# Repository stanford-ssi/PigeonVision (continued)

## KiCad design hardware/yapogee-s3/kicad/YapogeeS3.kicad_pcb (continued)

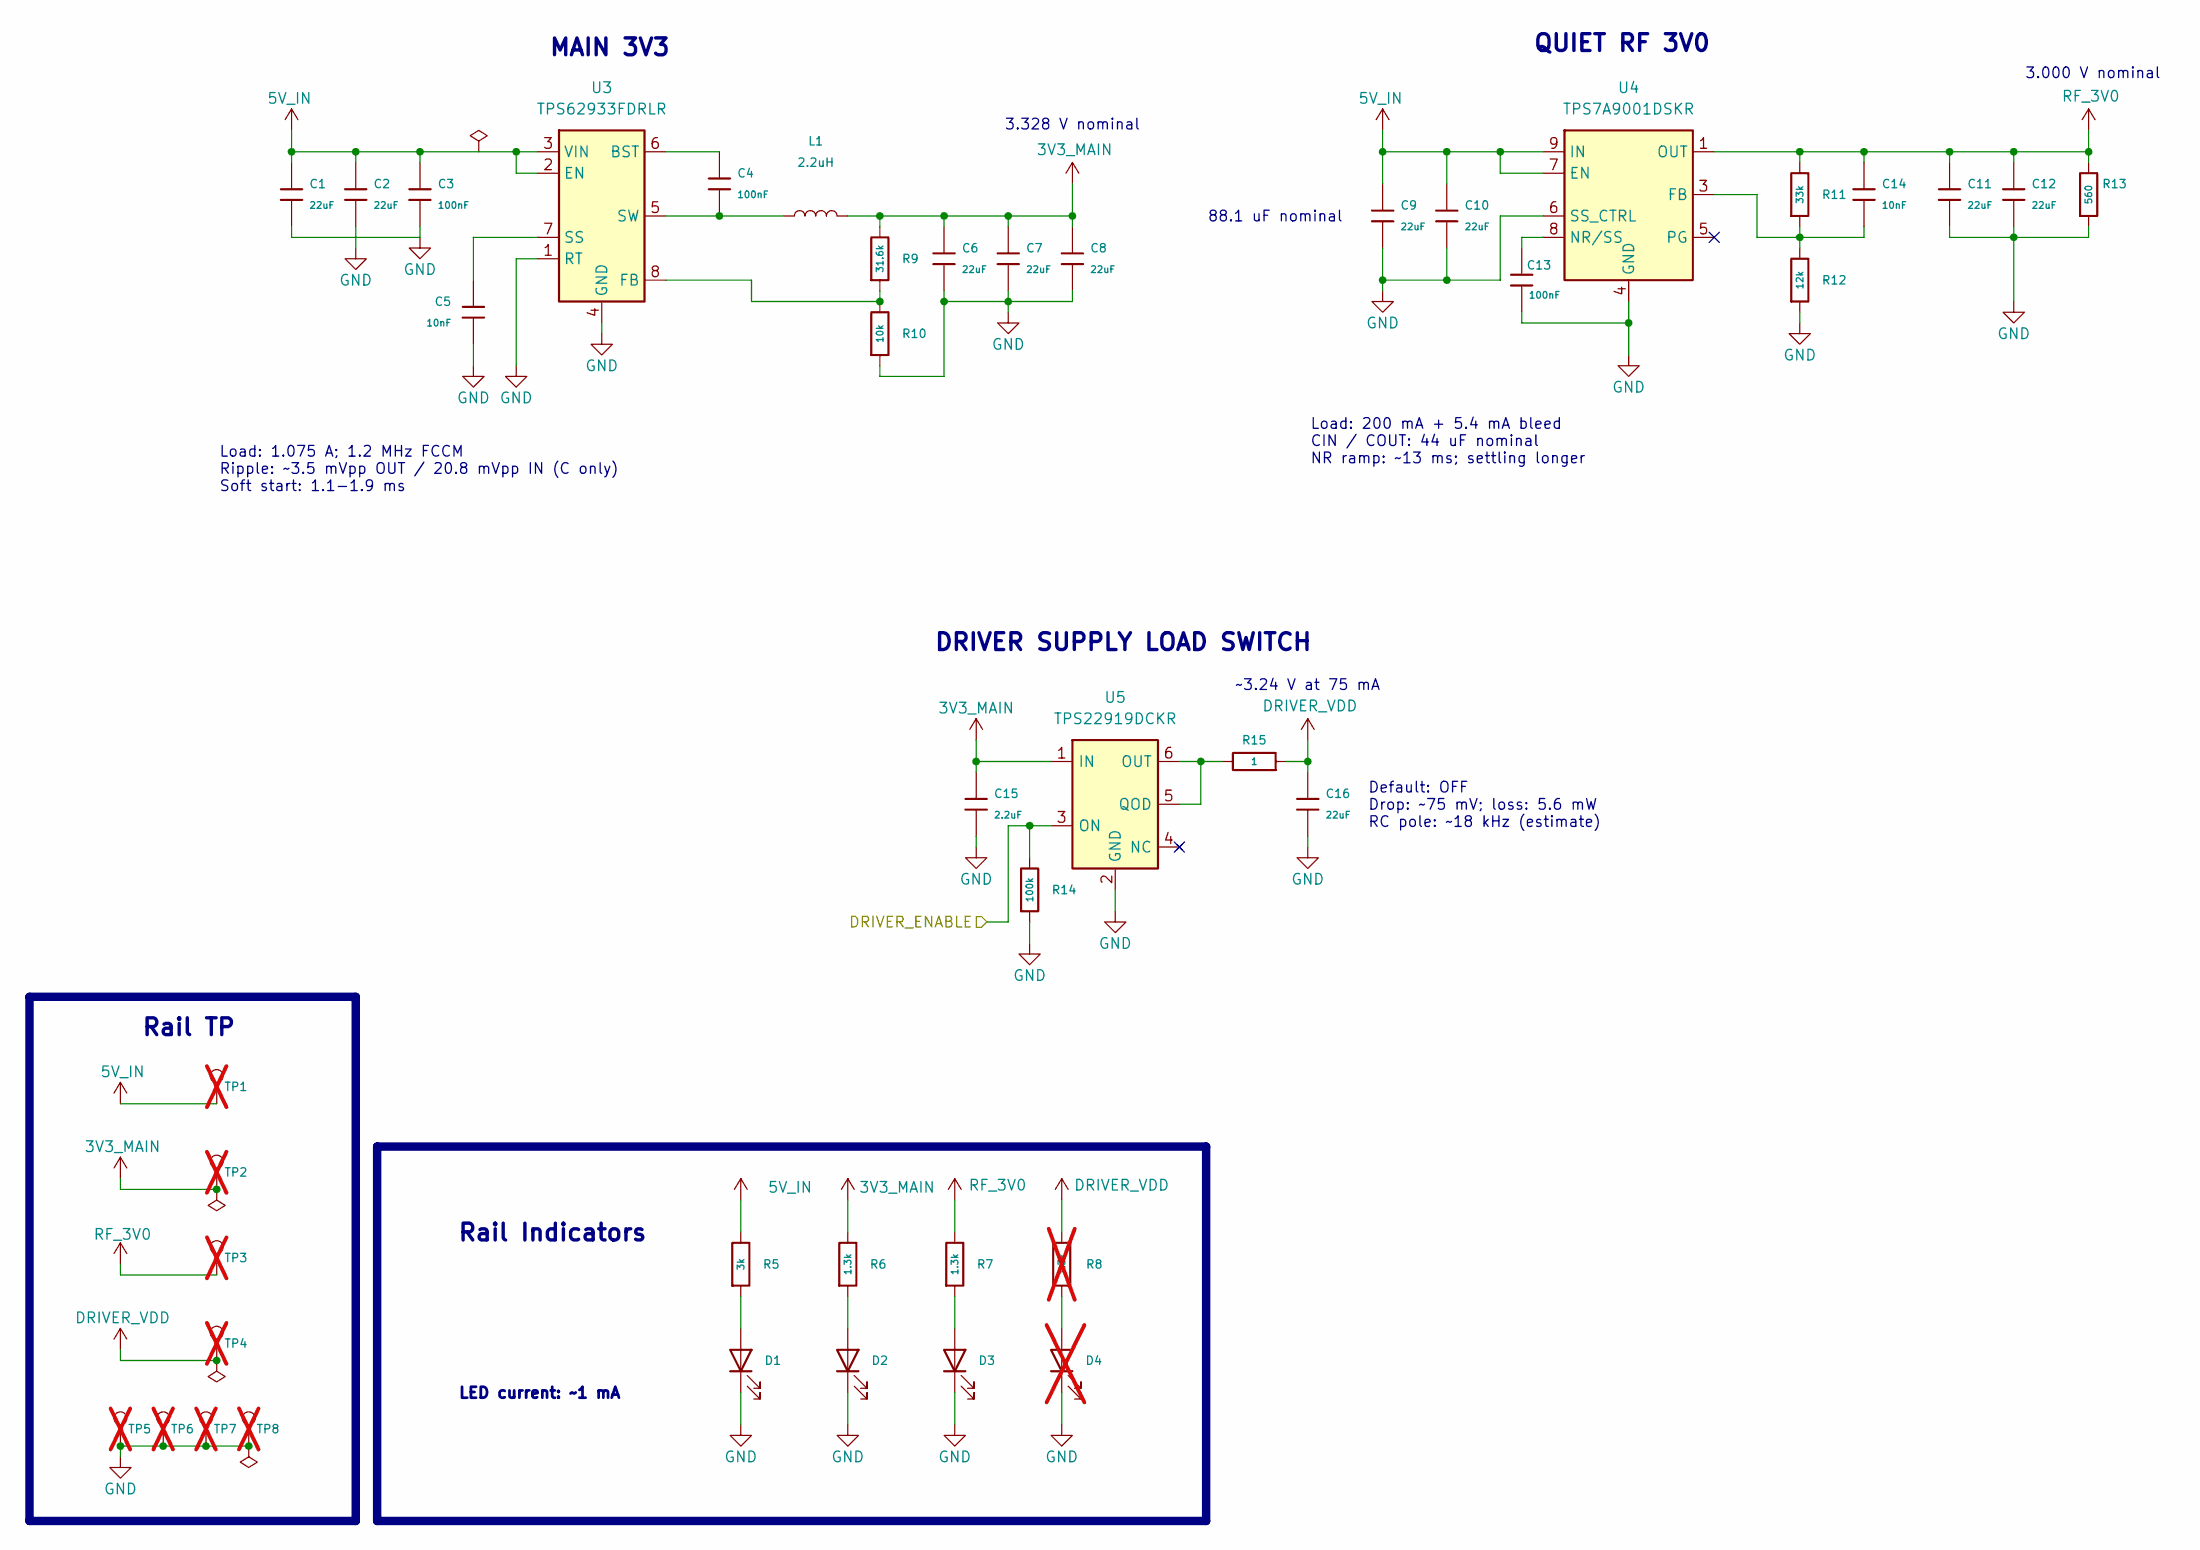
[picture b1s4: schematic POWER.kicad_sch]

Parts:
C1, C2, C6, C7, C8, C9, C10, C11, C12, C16: 22uF; C_Murata_GCM31_3216_RefReflow; Voltage Rated 10V; Tolerance ±10%; MPN GCM31CR71A226KE02L; LCSC C126598
C3, C4, C13: 100nF; C_Murata_GCM15_1005_RefReflow; Voltage Rated 50V; Tolerance ±10%; MPN GCM155R71H104KE02D; LCSC C85858
C5, C14: 10nF; C_Murata_GCM18_1608_RefReflow; Voltage Rated 50V; Tolerance ±5%; MPN GCM1885C1H103JA16D; LCSC C1517789
C15: 2.2uF; C_Kyocera_KAM15_1608_RefReflow; Voltage Rated 10V; Tolerance ±10%; MPN KAM15AR71A225KT; DigiKey Part # 478-KAM15AR71A225KTCT-ND
D1, D2, D3: LTST-C170KGKT; LiteOn_LTST-C170KGKT_0805; MPN LTST-C170KGKT; DigiKey Part # 160-1414-1-ND
D4: LTST-C170KGKT; LiteOn_LTST-C170KGKT_0805; MPN LTST-C170KGKT; DigiKey Part # 160-1414-1-ND; not fitted
L1: 2.2uH; Bourns_SRP5030TA; MPN SRP5030TA-2R2M
R5: 3k; KiCad_Resistor_SMD_R_0402_1005Metric; Tolerance ±1%; Part CRCW04023K00FKED
R6, R7: 1.3k; KiCad_Resistor_SMD_R_0402_1005Metric; Tolerance ±1%; Part CRCW04021K30FKED
R8: 1.3k; KiCad_Resistor_SMD_R_0402_1005Metric; Tolerance ±1%; Part CRCW04021K30FKED; not fitted
R9: 31.6k; KiCad_Resistor_SMD_R_0402_1005Metric; MPN RT0402BRD0731K6L
R10: 10k; KiCad_Resistor_SMD_R_0402_1005Metric; MPN RT0402BRD0710KL
R11: 33k; KiCad_Resistor_SMD_R_0402_1005Metric; MPN RT0402BRD0733KL
R12: 12k; KiCad_Resistor_SMD_R_0402_1005Metric; MPN RT0402BRD0712KL
R13: 560; KiCad_Resistor_SMD_R_0402_1005Metric; MPN RC0402FR-07560RL
R14: 100k; KiCad_Resistor_SMD_R_0402_1005Metric; MPN RC0402FR-07100KL
R15: 1; KiCad_Resistor_SMD_R_0402_1005Metric; MPN CRCW04021R00FKED
TP1: 5V_IN; TestPoint_Pad_D1.0mm; MPN PCB_TEST_PAD_1MM; not fitted
TP2: 3V3_MAIN; TestPoint_Pad_D1.0mm; MPN PCB_TEST_PAD_1MM; not fitted
TP3: RF_3V0; TestPoint_Pad_D1.0mm; MPN PCB_TEST_PAD_1MM; not fitted
TP4: DRIVER_VDD; TestPoint_Pad_D1.0mm; MPN PCB_TEST_PAD_1MM; not fitted
TP5, TP6, TP7, TP8: GND; TestPoint_Pad_D1.0mm; MPN PCB_TEST_PAD_1MM; not fitted
U3: TPS62933FDRLR; SOT-583-8; MPN TPS62933FDRLR; LCSC Part # C5219272
U4: TPS7A9001DSKR; TI_DSK0010A_TPS7A90; MPN TPS7A9001DSKR
U5: TPS22919DCKR; TI_DCK0006A_SC70-6_P0.65mm; MPN TPS22919DCKR; LCSC Part # C2149796

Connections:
3V3_MAIN: C6.1, C7.1, C8.1, C15.1, L1.2, R6.1, R9.1, TP2.1, U5.1 (IN); also elsewhere on the board
5V_IN: C1.1, C2.1, C3.1, C9.1, C10.1, R5.1, TP1.1, U3.2 (EN), U3.3 (VIN), U4.7 (EN), U4.9 (IN), U4.10 (IN); also elsewhere on the board
/MCU/DRIVER_ENABLE: R14.1, U5.3 (ON); also elsewhere on the board
DRIVER_VDD: C16.1, R8.1, R15.2, TP4.1; also elsewhere on the board
GND: C1.2, C2.2, C3.2, C5.2, C6.2, C7.2, C8.2, C9.2, C10.2, C11.2, C12.2, C13.2, C15.2, C16.2, D1.1 (K), D2.1 (K), D3.1 (K), D4.1 (K), R10.2, R12.2, R13.2, R14.2, TP5.1, TP6.1, TP7.1, TP8.1, U3.1 (RT), U3.4 (GND), U4.4 (GND), U4.6 (SS_CTRL), U4.11 (GND), U5.2 (GND); also elsewhere on the board
unnamed: D1.2 (A), R5.2
unnamed: D2.2 (A), R6.2
unnamed: D3.2 (A), R7.2
unnamed: D4.2 (A), R8.2
unnamed: C4.1, U3.6 (BST)
unnamed: R9.2, R10.1, U3.8 (FB)
unnamed: C5.1, U3.7 (SS)
unnamed: C4.2, L1.1, U3.5 (SW)
unnamed: C14.2, R11.2, R12.1, U4.3 (FB)
unnamed: C13.1, U4.8 (NR/SS)
unnamed: R15.1, U5.5 (QOD), U5.6 (OUT)
RF_3V0: C11.1, C12.1, C14.1, R7.1, R11.1, R13.1, TP3.1, U4.1 (OUT), U4.2 (OUT); also elsewhere on the board

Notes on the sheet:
Rail Indicators
88.1 uF nominal
Load: 1.075 A; 1.2 MHz FCCM Ripple: ~3.5 mVpp OUT / 20.8 mVpp IN (C only) Soft start: 1.1-1.9 ms
Rail TP
MAIN 3V3
DRIVER SUPPLY LOAD SWITCH
Load: 200 mA + 5.4 mA bleed CIN / COUT: 44 uF nominal NR ramp: ~13 ms; settling longer
QUIET RF 3V0
3.328 V nominal
~3.24 V at 75 mA
LED current: ~1 mA
3.000 V nominal
Default: OFF Drop: ~75 mV; loss: 5.6 mW RC pole: ~18 kHz (estimate)

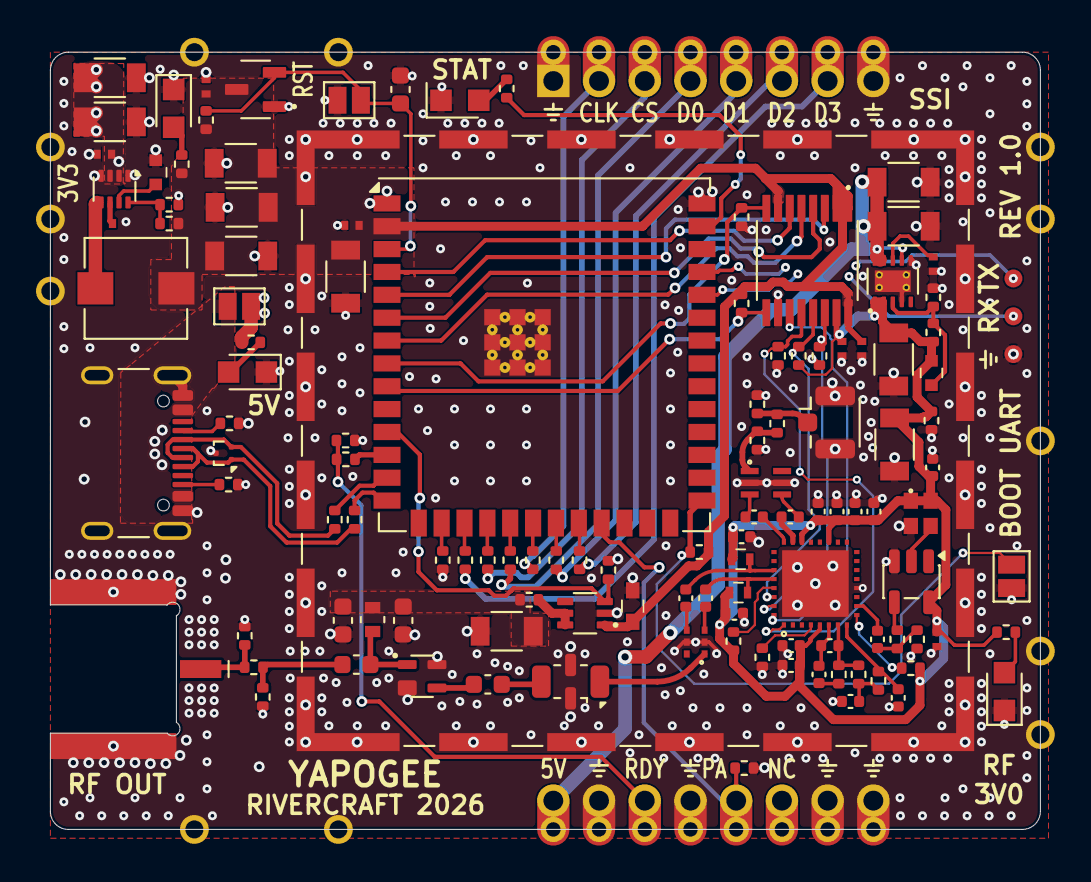
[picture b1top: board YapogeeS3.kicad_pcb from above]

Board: 4 copper layers, 55.0 x 43.2 mm, 124 parts (0 on the bottom side), 83 nets.

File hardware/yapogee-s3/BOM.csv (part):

block,references,quantity,value,manufacturer,mpn,package,population,symbol,footprint,datasheet
MCU,U1,1,"ESP32-S3 module,16MB QSPI flash,8MB octal PSRAM",Espressif,ESP32-S3-WROOM-1U-N16R8,18x19.2mm 40 perimeter pads + GND EP41,Fitted,PigeonVision:ESP32-S3-WROOM-1U-N16R8,PigeonVision:Espressif_ESP32_S3_WROOM_1U_18x19.2mm,https://www.espressif.com/sites/default/files/documentation/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
MCU,C17,1,100nF,Murata,GCM155R71H104KE02D,0402,Fitted,Yapogee_Power:GCM155R71H104KE02D,PigeonVision:C_Murata_GCM15_1005_RefReflow,https://pim.murata.com/asset/pim4/ceramicCapacitorSMD/GCM155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
MCU,C18,1,22uF,Murata,GCM31CR71A226KE02L,1206,Fitted,Yapogee_Power:GCM31CR71A226KE02L,PigeonVision:C_Murata_GCM31_3216_RefReflow,https://www.murata.com/en-us/products/productdetail?partno=G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
MCU,"R16,R17",2,10k,Yageo,RC0402FR-0710KL,0402,Fitted,PigeonVision:RC0402FR-0710KL,PigeonVision:KiCad_Resistor_SMD_R_0402_1005Metric,https://www.yageo.com/en/Chart/Download/pdf/RC0402
MCU,R18,1,10k,Yageo,RC0402FR-0710KL,0402,Fitted,PigeonVision:RC0402FR-0710KL,PigeonVision:KiCad_Resistor_SMD_R_0402_1005Metric,https://www.yageo.com/en/Chart/Download/pdf/RC0402
MCU,C19,1,1uF X7R 16V 10%,TDK,C1608X7R1C105K080AC,0603,Fitted,PigeonVision:C1608X7R1C105K080AC,PigeonVision:KiCad_Capacitor_SMD_C_0603_1608Metric,https://product.tdk.com/en/search/capacitor/ceramic/mlcc/inf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
MCU,U6,1,3.08V reset supervisor 200ms,Texas Instruments,TLV803EA30DBZR,SOT23-3 DBZ,Fitted,PigeonVision:TLV803EA30DBZR,PigeonVision:TI_DBZ0003A_TLV803E,https://www.ti.com/lit/ds/symlink/tlv803e.pdf
MCU,C21,1,100nF,Murata,GCM155R71H104KE02D,0402,Fitted,Yapogee_Power:GCM155R71H104KE02D,PigeonVision:C_Murata_GCM15_1005_RefReflow,https://pim.murata.com/asset/pim4/ceramicCapacitorSMD/GCM155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
USB,J2,1,USB-C2.0 power/data receptacle,GCT,USB4105-GF-A-060,16contact topmount;0.60mm shell stakes,Fitted,PigeonVision:USB4105-GF-A-060,PigeonVision:USB_C_Receptacle_GCT_USB4105_GF_A_16P,https://gct.co/files/drawings/usb4105.pdf
USB,U2,1,2-channel passive USB D+/D− ESD,Texas Instruments,TPD2EUSB30DRTR,"SOT-3 DRT,1.0x0.8mm body",Fitted,Yapogee:TPD2EUSB30DRTR,PigeonVision:TI_DRT0003A_TPD2EUSB30,https://www.ti.com/lit/ds/symlink/tpd2eusb30.pdf
USB,"R3,R4",2,22,Yageo,RC0402FR-0722RL,0402,Fitted,PigeonVision:RC0402FR-0722RL,PigeonVision:KiCad_Resistor_SMD_R_0402_1005Metric,https://www.yageo.com/en/Chart/Download/pdf/RC0402
INTERFACE,U9,1,RF mixer control level isolation,Texas Instruments,SN74AXC4T774PWR,TSSOP16 PW,Fitted,PigeonVision:SN74AXC4T774PWR,PigeonVision:TI_PW0016A_SN74AXC4T774,https://www.ti.com/lit/ds/symlink/sn74axc4t774.pdf
INTERFACE,"C28,C29",2,100nF,Murata,GCM155R71H104KE02D,0402,Fitted,Yapogee_Power:GCM155R71H104KE02D,PigeonVision:C_Murata_GCM15_1005_RefReflow,https://pim.murata.com/asset/pim4/ceramicCapacitorSMD/GCM155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
INTERFACE,R21,1,4.7k,Yageo,RC0402FR-074K7L,0402,Fitted,PigeonVision:RC0402FR-074K7L,PigeonVision:KiCad_Resistor_SMD_R_0402_1005Metric,https://www.yageo.com/en/Chart/Download/pdf/RC0402
INTERFACE,R22,1,10k,Yageo,RC0402FR-0710KL,0402,Fitted,PigeonVision:RC0402FR-0710KL,PigeonVision:KiCad_Resistor_SMD_R_0402_1005Metric,https://www.yageo.com/en/Chart/Download/pdf/RC0402
INTERFACE,R23,1,100k,Yageo,RC0402FR-07100KL,0402,Fitted,PigeonVision:RC0402FR-07100KL,PigeonVision:KiCad_Resistor_SMD_R_0402_1005Metric,https://www.yageo.com/en/Chart/Download/pdf/RC0402
INTERFACE,"R26,R27,R28,R29,R30,R31,R32",7,33,Yageo,RC0402FR-0733RL,0402,Fitted,PigeonVision:RC0402FR-0733RL,PigeonVision:KiCad_Resistor_SMD_R_0402_1005Metric,https://www.yageo.com/en/Chart/Download/pdf/RC0402
INTERFACE,R33,1,4.7k,Yageo,RC0402FR-074K7L,0402,Fitted,PigeonVision:RC0402FR-074K7L,PigeonVision:KiCad_Resistor_SMD_R_0402_1005Metric,https://www.yageo.com/en/Chart/Download/pdf/RC0402
INTERFACE,"R34,R35",2,10k,Yageo,RC0402FR-0710KL,0402,Fitted,PigeonVision:RC0402FR-0710KL,PigeonVision:KiCad_Resistor_SMD_R_0402_1005Metric,https://www.yageo.com/en/Chart/Download/pdf/RC0402
Interface,R36,1,100k,Yageo,RC0402FR-07100KL,0402,Fitted,PigeonVision:RC0402FR-07100KL,PigeonVision:KiCad_Resistor_SMD_R_0402_1005Metric,https://www.yageo.com/en/
USB,"R1,R2",2,5.1k,Yageo,RC0402FR-075K1L,0402,Fitted,Yapogee:RC0402FR-075K1L,PigeonVision:KiCad_Resistor_SMD_R_0402_1005Metric,https://www.lcsc.com/datasheet/lcsc_datasheet_2206010045_UNI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
MCU,D5,1,green rail/status LED,Lite-On,LTST-C170KGKT,0805,Fitted,Yapogee_Power:LTST-C170KGKT,PigeonVision:LiteOn_LTST-C170KGKT_0805,https://optoelectronics.liteon.com/upload/download/DS22-2000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
MCU,R19,1,1k,Yageo,RC0402FR-071KL,0402,Fitted,PigeonVision:RC0402FR-071KL,PigeonVision:KiCad_Resistor_SMD_R_0402_1005Metric,https://www.yageo.com/en/Chart/Download/pdf/RC0402
POWER,"C1,C2,C6,C7,C8,C9,C11,C16",8,22uF,Murata,GCM31CR71A226KE02L,1206,Fitted,Yapogee_Power:GCM31CR71A226KE02L,PigeonVision:C_Murata_GCM31_3216_RefReflow,https://www.murata.com/en-us/products/productdetail?partno=G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
POWER,"C3,C4,C13",3,100nF,Murata,GCM155R71H104KE02D,0402,Fitted,Yapogee_Power:GCM155R71H104KE02D,PigeonVision:C_Murata_GCM15_1005_RefReflow,https://pim.murata.com/asset/pim4/ceramicCapacitorSMD/GCM155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
POWER,"C5,C14",2,10nF,Murata,GCM1885C1H103JA16D,0603,Fitted,Yapogee_Power:GCM1885C1H103JA16D,PigeonVision:C_Murata_GCM18_1608_RefReflow,https://pim.murata.com/asset/pim4/ceramicCapacitorSMD/GCM188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
POWER,"C10,C12",2,22uF,Murata,GCM31CR71A226KE02L,1206,Fitted,Yapogee_Power:GCM31CR71A226KE02L,PigeonVision:C_Murata_GCM31_3216_RefReflow,https://www.murata.com/en-us/products/productdetail?partno=G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
POWER,C15,1,2.2uF,KYOCERA AVX,KAM15AR71A225KT,0603,Fitted,Yapogee_Power:KAM15AR71A225KT,PigeonVision:C_Kyocera_KAM15_1608_RefReflow,https://spec.ele.kyocera.com/specifications/KAM15AR71A225KT.pdf
POWER,"D1,D2,D3,D4",4,LTST-C170KGKT,Lite-On,LTST-C170KGKT,0805,Fitted,Yapogee_Power:LTST-C170KGKT,PigeonVision:LiteOn_LTST-C170KGKT_0805,https://optoelectronics.liteon.com/upload/download/DS22-2000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
POWER,L1,1,2.2uH,Bourns,SRP5030TA-2R2M,5.7±0.3 x5.2±0.2 x2.8±0.2mm SMD,Fitted,Yapogee_Power:SRP5030TA-2R2M,PigeonVision:Bourns_SRP5030TA,https://www.bourns.com/docs/product-datasheets/srp5030ta.pdf
POWER,R5,1,3k,Vishay,CRCW04023K00FKED,0402,Fitted,Yapogee_Power:CRCW04023K00FKED,PigeonVision:KiCad_Resistor_SMD_R_0402_1005Metric,https://www.vishay.com/doc?20035=
POWER,"R6,R7,R8",3,1.3k,Vishay,CRCW04021K30FKED,0402,Fitted,Yapogee_Power:CRCW04021K30FKED,PigeonVision:KiCad_Resistor_SMD_R_0402_1005Metric,https://www.vishay.com/doc?20035=
POWER,R9,1,31.6k,Yageo,RT0402BRD0731K6L,0402,Fitted,PigeonVision:RT0402BRD0731K6L,PigeonVision:KiCad_Resistor_SMD_R_0402_1005Metric,https://www.yageo.com/en/Chart/Download/pdf/RT0402
POWER,R10,1,10k,Yageo,RT0402BRD0710KL,0402,Fitted,PigeonVision:RT0402BRD0710KL,PigeonVision:KiCad_Resistor_SMD_R_0402_1005Metric,https://www.yageo.com/en/Chart/Download/pdf/RT0402
POWER,R11,1,33k,Yageo,RT0402BRD0733KL,0402,Fitted,PigeonVision:RT0402BRD0733KL,PigeonVision:KiCad_Resistor_SMD_R_0402_1005Metric,https://www.yageo.com/en/Chart/Download/pdf/RT0402
POWER,R12,1,12k,Yageo,RT0402BRD0712KL,0402,Fitted,PigeonVision:RT0402BRD0712KL,PigeonVision:KiCad_Resistor_SMD_R_0402_1005Metric,https://www.yageo.com/en/Chart/Download/pdf/RT0402
POWER,R13,1,560,Yageo,RC0402FR-07560RL,0402,Fitted,PigeonVision:RC0402FR-07560RL,PigeonVision:KiCad_Resistor_SMD_R_0402_1005Metric,https://www.yageo.com/en/Chart/Download/pdf/RC0402
POWER,R14,1,100k,Yageo,RC0402FR-07100KL,0402,Fitted,PigeonVision:RC0402FR-07100KL,PigeonVision:KiCad_Resistor_SMD_R_0402_1005Metric,https://www.yageo.com/en/Chart/Download/pdf/RC0402
POWER,R15,1,1,Vishay Dale,CRCW04021R00FKED,0402,Fitted,PigeonVision:CRCW04021R00FKED,PigeonVision:KiCad_Resistor_SMD_R_0402_1005Metric,https://www.vishay.com/docs/20035/dcrcwe3.pdf
POWER,U3,1,TPS62933FDRLR,Texas Instruments,TPS62933FDRLR,SOT583-8 DRL,Fitted,PigeonVision:TPS62933FDRLR,PigeonVision:SOT-583-8,https://www.ti.com/lit/ds/symlink/tps62933.pdf
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
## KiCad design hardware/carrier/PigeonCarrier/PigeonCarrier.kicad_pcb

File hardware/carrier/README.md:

# Carrier

[Rev 1.1 fabrication and assembly files](production/Rev1.1/README.md)

**Current plan:** one CM5, two cameras, SPI to [Yapogee S3](../yapogee-s3/README.md) and Ethernet for service or the E200 fallback. Yapogee uses an ESP32-S3-WROOM-1U-N16R8 module and converts its RF output to 1.28 GHz. The PA and filter are on a separate board. Record to eMMC. Use a 3S 5 Ah battery with a one-hour planning target including pad time. Carrier diameter is 5.7 in (144.78 mm).

[Edit diagram](block-diagram.drawio) · [KiCad project](PigeonCarrier/PigeonCarrier.kicad_pro) · [Design master](../../calculations/design-master.xlsx)

| Block | Parts / connection |
| --- | --- |
| Compute | SC1596 / CM5104064: 4 GB RAM, 64 GB eMMC |
| CM5 connectors | 2 × Amphenol 10164227-1001A1RLF, 1.5 mm stack |
| Cameras | 2 × FRAMOS IMX900 + CIL212; retain the working FRAMOS adapters. J7/J8 use vertical Hirose FH12-22S-0.5SVA(54) FFC connectors with CM5IO-style pinout |
| Input protection | LM74502DDFR, 2 × CSD18540Q5B, SMBJ18CA; unfused input |
| Main 5 V | LM61495RPHR; CM5 and Yapogee, with E200 as an alternate transmitter |
| RF 5 V | TPS62933FDRLR; separate supply, default off |
| Camera rail | TPS62933FDRLR: shared 3V3_CAM from VBAT, enabled by 3V3_CM5; adapter boards provide camera-specific rails |
| Battery monitor | INA226AIDGSR + WSL25125L000FEA18, 5 mΩ |
| Sensors | BMI088, BMP581 and INA226 on CM5 GPIO2/3 I²C; polling without interrupt wiring |
| Camera control | Dedicated CM5 camera I²C lines; CAM0_RST from J1.97 and CAM1_RST from J1.100. Synchronization access reserved, synchronized exposures not required |
| Ethernet | EDAC A70-112-331N126 with integrated magnetics |
| Service | USB-C data/recovery, nRPIBOOT shunt, PWR_BUT button, J12 debug UART and CM5 activity LED on carrier; separate USB-C, BOOT, reset and UART access on Yapogee |
| Flight UART | Receive required; return TX optional. Logic voltage, connector and protocol TBD |

Both camera connectors receive the shared 3V3_CAM rail; MIPI connects directly to CM5. Keep the working adapter boards and their camera-specific power sequencing. The carrier does not replace their internal regulator circuitry.

Sensors use CM5 3.3 V. Yapogee receives 5V_MAIN through castellations and makes its own 3.328 V main and quiet 3.0 V rails. Reserve 1.5 A for the daughterboard. Its USB-C port supports standalone power before installation from a known 5 V source providing at least 1.5 A. Once mounted, leave JP1 open and use USB for data only while the carrier is on. Independent Pi PMIC-off operation is unsupported. The selected GRF5613 PA uses the separate switched 5V_RF rail. Keep space, 5 V power and Ethernet for the E200 fallback. The bench input is a PJ-102AH barrel jack beside the battery connector, used with the battery unplugged.

J1 uses vertical AMASS XT60PB-M30.G.Y: pin 1, at the keyed end marked −, is GND; pin 2, at the flat end marked +, is VBAT_RAW. J6 and both camera connectors are also vertical. USB-C J10 and the PJ-102AH bench input J2 remain horizontal. [Connector geometry, sourcing and model limits](../libraries/review/vertical-connectors.md).

J13 is the 55 × 43.18 mm Yapogee landing below the CM5. Its 28 lands match the module castellations, including twelve extra GND anchors. The footprint omits paste for hand soldering. The closed SMA pocket measures 33 × 12 mm with R1.5 corners and leaves about 11.3 mm of board at the narrowest point of the outer rim. It clears the body of the Amphenol 135103-01-06.00 elbow as it first meets the jack with the cable pointing up. Check the mating sequence, wrench access and cable bend in the flight stack before fabrication. [Cable assembly](https://www.amphenolrf.com/en-us/part/135103-01-06-00/5975/) The E200 stays available as a separate placement option. [Module interface](../yapogee-s3/interfaces.md)

| Signal | CM5 GPIO | CM5 J3 pad | Yapogee J1 / carrier J13 pad |
| --- | ---: | ---: | ---: |
| SCLK | 11 | 38 | 2 |
| D0 / MOSI | 10 | 44 | 5 |
| D1 | 9 | 40 | 7 |
| CS_N | 8 | 39 | 4 |
| READY | 25 | 41 | 11 |
| PA request into Pi | 22 | 46 | 13 |
| 5V_MAIN | — | — | 3 |
| D2 and D3, reserved for quad | — | — | 8, 10 |
| Reserved | — | — | 14 |

R42 pulls CS_N up to 3V3_CM5 with 4.7 kΩ. The CM5 and Yapogee share ground and use direct 3.3 V I/O. Power the installed Yapogee from 5V_MAIN and keep JP1 open. Coordinate GPIO startup and shutdown to avoid driving an unpowered endpoint.

Single-lane SPI0 is the bring-up mode. D1 provides a path to dual transmit with driver and firmware changes. Native SPI0 quad needs GPIO0 and GPIO1, which are assigned to CAM1 I²C. A quad implementation needs a different pin or host-peripheral plan and bench validation. [CM5 GPIO mux](https://datasheets.raspberrypi.com/cm5/cm5-datasheet.pdf)

GPIO17 / J3.50 switches the RF buck through 5V_RF_EN and retains its 10 kΩ pull-down. GPIO22 / J3.46 receives the Yapogee request. GPIO23 / J3.47 drives the separate, active-high PA_BIAS_EN signal.

The top sheet shows the six CM5-to-Yapogee signals and the separate PA bias enable wire. J14 is the vertical Molex 0430450418 Micro-Fit 3.0 header. Pin 1 supplies 5V_RF (4.88 V nominal), pins 2 and 4 are ground, and pin 3 carries PA_BIAS_EN. The PA board pulls pin 3 low by default and handles the GRF5613 shutdown polarity locally. J14 sits beside the RF buck and uses the same Molex STEP model as the PA board. PA control firmware remains pending. [PA harness and power](../rf-frontend/README.md)

J12 is a JST SH BM03B-SRSS-TB debug UART on CM5 GPIO14/15 using the Raspberry Pi debug-connector pinout: 1 RX into the CM5 (GPIO15), 2 GND, 3 TX from the CM5 (GPIO14). A Raspberry Pi Debug Probe plugs in with a straight-through cable. Both lines have 1 kΩ series resistors. The specification calls for 100 Ω, but CM5 GPIO pads are not failsafe, so the larger value limits back-feed from a powered probe into an unpowered CM5. LED4 (via R41, 220 Ω from 3V3_CM5) shows CM5 activity on LED_nACT.

CM5 configuration implied by this carrier: set `PSU_MAX_CURRENT=5000` in the bootloader EEPROM, because CC1/CC2 are unconnected and no USB-PD negotiation occurs. Set `enable_uart=1` for a Linux console on J12. Set `force_eeprom_read=0`, because ID_SD/ID_SC carry the CAM1 I²C bus.

Power control: J6 on Regulators uses vertical AMASS XT30UPB-M.G.Y. Pin 1 connects directly to U1 pin 1 (EN/UVLO / PWR_EN); pin 2 is GND. This dry-contact switch intentionally uses the connector's −-marked end for PWR_EN and +-marked end for GND; the moulded signs do not describe supply polarity. Use the microswitch COM and NO terminals: with the pin inserted and the lever pressed, closed contacts ground EN/UVLO and turn power off. Removing the pin releases the lever and opens the contact, allowing the existing UVLO divider to enable power. Confirm that the actual mechanism gives these contact states. An unplugged switch also allows power. This is not a latch: shut down the CM5 before reinserting the pin.

Q4, R39 and R40 were removed from the schematic and unrouted PCB. At 12.6 V, the closed contact carries 12.6 V / 7.5 kΩ = 1.68 mA through R2; R2 dissipates 21.2 mW. The existing UVLO and OV dividers remain unchanged. Total off-state divider draw is about 1.89 mA, plus controller current and leakage. Off disables downstream battery power; it does not isolate the battery or eliminate standby current. Switch contact quality, bounce and startup remain bench checks. [LM74502 datasheet](https://www.ti.com/lit/ds/symlink/lm74502.pdf).

Camera, sensor, Ethernet and USB/service hierarchy is connected, along with CM5 power/grounds and both regulator enables. The carrier USB-C port uses host VBUS only for data-switch control, with no connection to the battery or 5 V power rail. Its ESD footprint uses explicit external copper connections from each protected pad to the opposite NC pad. USB enumeration, recovery and power transitions remain hardware checks. The cooler fan header uses the native CM5 PWM/tach interface with 5V_MAIN supply.

The 2026-10-06 direct-switch check reported no ERC errors or warnings. All 200 CM5 contacts were connected or intentionally marked unused. The switch change affected only J6.1 among the retained component connections. Power-source flags identify feeds through passive parts, including U7's internally charged bootstrap node. Switch contact states, camera adapter current and sequencing, XT60 fit, power transitions and final layout remain to be checked. [Switch verification](../../build/pull-pin-direct-2026-10-06/verification.json) · [Connection review](../../build/carrier-closeout-2026-10-05/connection-review.json) · [Footprint review](../../build/carrier-closeout-2026-10-05/all-footprints-audit.json)

## Routing

Use **JLC06161H-3313**, 1.6 mm nominal, 1 oz outer and 0.5 oz inner copper. Route signals on F.Cu, L3 (In2.Cu) and B.Cu. Reserve L2 (In1.Cu), L4 (In3.Cu) and L5 (In4.Cu) for continuous GND. Add and fill those zones during layout.

| Net class | Outer width / gap | L3 width / gap | P/N skew |
| --- | --- | --- | --- |
| CSI and Ethernet, 100 Ω | 0.150 / 0.500 mm | 0.125 / 0.300 mm | 0.15 mm max |
| USB 2.0, 90 Ω | 0.175 / 0.300 mm | 0.160 / 0.300 mm | 0.15 mm max |
| Single ended, 50 Ω | 0.160 mm | 0.140 mm | n/a |

Layer rules select the L3 geometry automatically. SPI SCLK, D0, D1 and CS_N use SE_50R; I²C, UART and slow controls keep their normal classes. Power widths remain starting values: 1.50 mm battery, 1.00 mm 5 V and 0.50 mm 3.3 V. Use short outer-layer pours for the high-current paths.

Route CAM1 west of the SMA pocket. Keep the CM5 launch short before opening to the ordinary pair gap. Copper-to-edge clearance remains 0.50 mm. Use 0.45 mm via lands with 0.30 mm drills for controlled-impedance nets and 0.60 / 0.30 mm for general routing. The smaller vias fit the camera connector lands but need a staggered escape from the 0.20 mm-wide CM5 lands. No blind, buried or laser microvias are enabled.

The outer model references L2 or L5; L3 references L2 and L4. Keep other same-layer copper 0.50 mm away outside the reviewed launches. Match P/N within each pair and keep each camera's long runs on the same layer where practical. Review clock-to-data skew before tuning; the CM5 datasheet provides no numeric CSI interlane limit. [Calculations](routing-plan.json) · [Fabrication notes](fabrication-notes.md) · [CM5 datasheet](https://datasheets.raspberrypi.com/cm5/cm5-datasheet.pdf)

The BMP581 uses the shared solder mask opening recommended by Bosch. Keep exposed copper under the sensor limited to its intended pads and escapes. [BMP581 datasheet](https://www.bosch-sensortec.com/media/boschsensortec/downloads/datasheets/bst-bmp581-ds004.pdf)

The design master still budgets E200 power. Reconcile it with the accepted 1.5 A Yapogee allocation on 5V_MAIN, keeping E200 as an alternative rather than adding both transmitter loads to one flight configuration. GRF5613 is selected for PA planning; its loaded current and thermal performance remain unmeasured. Confirm mounting and connector access before final layout.

[Library and sourcing](../libraries/README.md) · [CM5 datasheet](https://datasheets.raspberrypi.com/cm5/cm5-datasheet.pdf) · [Camera datasheet](https://www.mouser.com/catalog/specsheets/FRAMOS_2-12-2026_FSM.GO-IMX900_Datasheet_v1.2a.pdf)

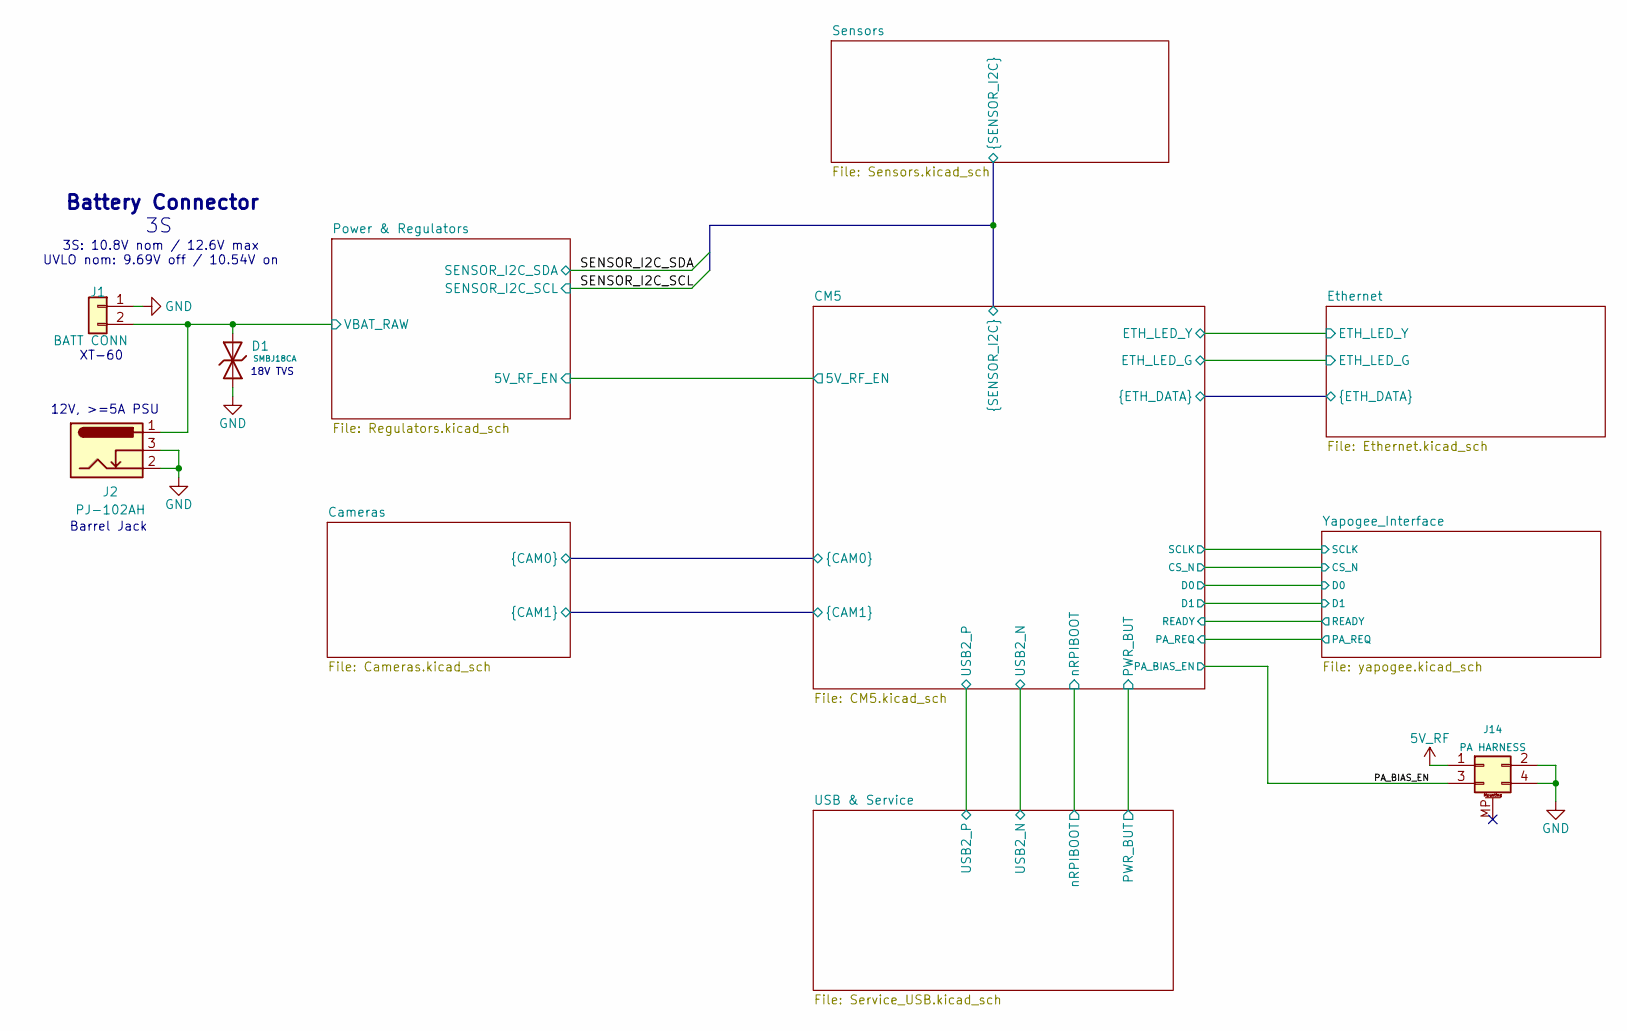
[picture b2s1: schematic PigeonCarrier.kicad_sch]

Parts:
D1: SMBJ18CA; D_SMB; Part SMBJ18CA; LCSC C19077574
J1: BATT CONN; AMASS_XT60PB-M_1x02_P7.20mm_Vertical_2025; MPN XT60PB-M30.G.Y; LCSC C19268037
J2: PJ-102AH; SameSky_PJ-102AH_Horizontal; Voltage / Current Rating 24 V / 5 A (manufacturer); MPN PJ-102AH; DigiKey Part # CP-102AH-ND
J14: PA HARNESS; Molex_Micro-Fit_3.0_43045-0418_2x02-1MP_P3.00mm_Vertical; MPN 0430450418

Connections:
5V_RF: J14.1 (5V_RF); also elsewhere on the board
/PA_BIAS_EN: J14.3 (PA_BIAS_EN); also elsewhere on the board
/Power & Regulators/VBAT_RAW: D1.2, J1.2, J2.1 (Center); also elsewhere on the board
GND: D1.1, J1.1, J2.2 (Sleeve), J2.3 (Sleeve_Shunt), J14.2 (GND), J14.4 (GND); also elsewhere on the board

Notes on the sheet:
Barrel Jack
Battery Connector
XT-60
3S: 10.8V nom / 12.6V max UVLO nom: 9.69V off / 10.54V on
18V TVS
12V, >=5A PSU

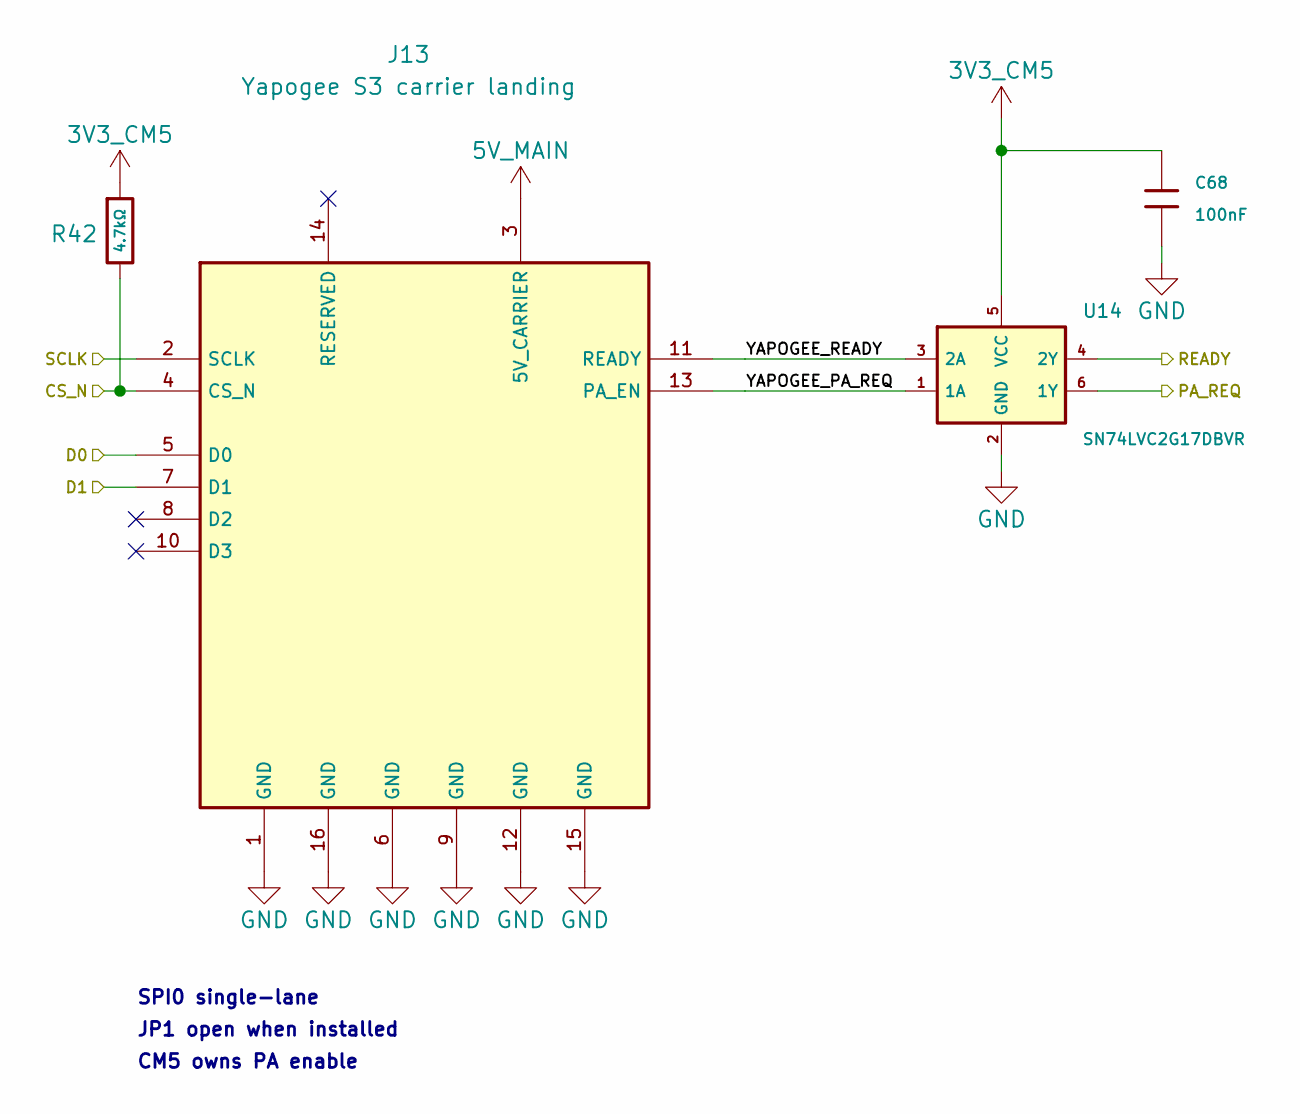
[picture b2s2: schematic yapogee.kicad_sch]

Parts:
C68: 100nF; C_0402; Voltage Rated 50V; Tolerance u00b110%; Part CL05B104KB54PNC; LCSC C307331
J13: Yapogee S3 carrier landing; YapogeeS3_CarrierLanding16_55x43p18_P2p54_GND12
R42: 4.7kΩ; R_0402; Overload Voltage (Max) 50V; Tolerance ±1%; Part 0402WGF4701TCE; LCSC C25900
U14: SN74LVC2G17DBVR; SOT-23-6; MPN SN74LVC2G17DBVR; LCSC C10429

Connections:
3V3_CM5: C68.1, R42.1, U14.5 (VCC); also elsewhere on the board
5V_MAIN: J13.3 (5V_CARRIER); also elsewhere on the board
/CM5/CS_N: J13.4 (CS_N), R42.2; also elsewhere on the board
/CM5/D0: J13.5 (D0); also elsewhere on the board
/CM5/D1: J13.7 (D1); also elsewhere on the board
/CM5/PA_REQ: U14.6 (1Y); also elsewhere on the board
/CM5/READY: U14.4 (2Y); also elsewhere on the board
/CM5/SCLK: J13.2 (SCLK); also elsewhere on the board
/Yapogee_Interface/YAPOGEE_PA_REQ: J13.13 (PA_EN), U14.1 (1A)
/Yapogee_Interface/YAPOGEE_READY: J13.11 (READY), U14.3 (2A)
GND: C68.2, J13.1 (GND), J13.6 (GND), J13.9 (GND), J13.12 (GND), J13.15 (GND), J13.16 (GND), U14.2 (GND); also elsewhere on the board

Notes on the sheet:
JP1 open when installed
SPI0 single-lane
CM5 owns PA enable

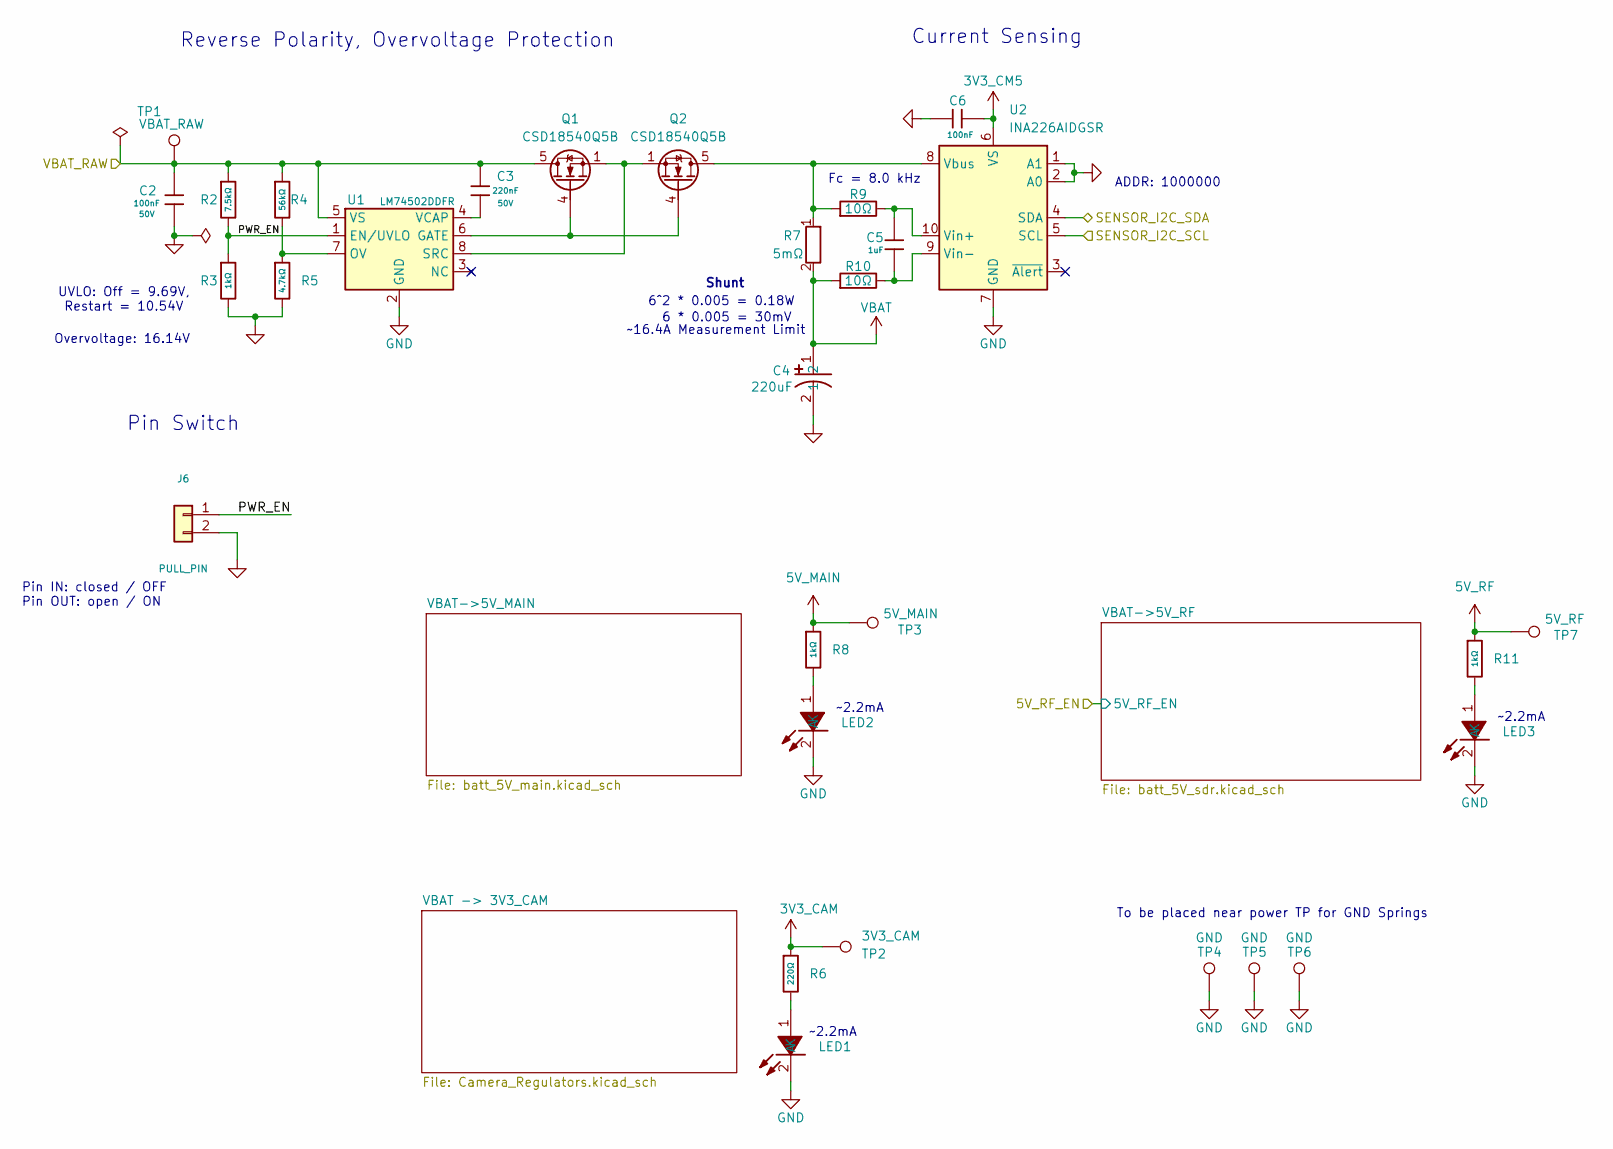
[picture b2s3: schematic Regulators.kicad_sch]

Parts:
C2, C6: 100nF; C_0402; Voltage Rated 50V; Tolerance ±10%; Part CL05B104KB54PNC; LCSC C307331
C3: 220nF; C_0805; Voltage Rated 50V; Tolerance ±10%; Part CL21B224KBFNNNE; LCSC C5378
C4: 220uF; Panasonic_EEE-FK1V221P_CaseF_8x10.2mm; Manufacturer Part EEEFK1V221P; LCSC C178562
C5: 1uF; C_0805; Voltage Rated 50V; Tolerance ±10%; Part CL21B105KBFNNNE; LCSC C28323
J6: PULL_PIN; AMASS_XT30UPB-M_1x02_P5.00mm_Vertical_2025; MPN XT30UPB-M.G.Y; LCSC Part # C428721
LED1, LED2, LED3: 0805G_Green; Manufacturer Part KT-0805G; LCSC C2297
Q1, Q2: CSD18540Q5B; TI_CSD18540Q5B_Q5B; MPN CSD18540Q5B; LCSC C86513
R2: 7.5kΩ; R_0402; Overload Voltage (Max) 50V; Tolerance ±1%; Part 0402WGF7501TCE; LCSC C25918
R3, R8, R11: 1kΩ; R_0402; Overload Voltage (Max) 50V; Tolerance ±1%; Part 0402WGF1001TCE; LCSC C11702
R4: 56kΩ; R_0402; Overload Voltage (Max) 50V; Tolerance ±1%; Part 0402WGF5602TCE; LCSC C25796
R5: 4.7kΩ; R_0402; Overload Voltage (Max) 50V; Tolerance ±1%; Part 0402WGF4701TCE; LCSC C25900
R6: 220Ω; R_0402; Overload Voltage (Max) 50V; Tolerance ±1%; Part 0402WGF2200TCE; LCSC C25091
R7: 5mΩ; Vishay_WSL2512_5mOhm_2W; Tolerance ±1%; Power Rating 2 W at 70 °C; MPN WSL25125L000FEA18; LCSC Part # C844694
R9, R10: 10Ω; R_0402; Overload Voltage (Max) 50V; Tolerance ±1%; Manufacturer Part 0402WGF100JTCE; LCSC C25077
TP1: VBAT_RAW; TestPoint_Pad_D2.0mm
TP2: 3V3_CAM; TestPoint_Pad_D2.0mm
TP3: 5V_MAIN; TestPoint_Pad_D2.0mm
TP4, TP5, TP6: GND; TestPoint_Pad_D2.0mm
TP7: 5V_RF; TestPoint_Pad_D2.0mm
U1: LM74502DDFR; Texas_DDF0008A_SOT-8_1.6x2.9mm_P0.65mm; MPN LM74502DDFR; LCSC Part # C3236215
U2: INA226AIDGSR; TI_DGS0010A_VSSOP-10_3x3mm_P0.5mm; MPN INA226AIDGSR; LCSC Part # C49851

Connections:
3V3_CAM: R6.1, TP2.1 (1_1); also elsewhere on the board
3V3_CM5: C6.1, U2.6 (VS); also elsewhere on the board
5V_MAIN: R8.1, TP3.1 (1_1); also elsewhere on the board
5V_RF: R11.1, TP7.1 (1_1); also elsewhere on the board
/Power & Regulators/PWR_EN: J6.1, R2.2, R3.1, U1.1 (EN/UVLO)
/Power & Regulators/VBAT_RAW: C2.1, C3.1, Q1.5 (D), R2.1, R4.1, TP1.1 (1_1), U1.5 (VS); also elsewhere on the board
/Sensors/SENSOR_I2C_SCL: U2.5 (SCL); also elsewhere on the board
/Sensors/SENSOR_I2C_SDA: U2.4 (SDA); also elsewhere on the board
GND: C2.2, C4.2, C6.2, J6.2, LED1.2 (K), LED2.2 (K), LED3.2 (K), R3.2, R5.2, TP4.1 (1_1), TP5.1 (1_1), TP6.1 (1_1), U1.2 (GND), U2.1 (A1), U2.2 (A0), U2.7 (GND); also elsewhere on the board
unnamed: LED1.1 (A), R6.2
unnamed: LED2.1 (A), R8.2
unnamed: LED3.1 (A), R11.2
unnamed: Q1.4 (G), Q2.4 (G), U1.6 (GATE)
unnamed: Q2.5 (D), R7.1, R9.1, U2.8 (Vbus)
unnamed: R4.2, R5.1, U1.7 (OV)
unnamed: Q1.1 (S), Q1.2 (S), Q1.3 (S), Q2.1 (S), Q2.2 (S), Q2.3 (S), U1.8 (SRC)
unnamed: C3.2, U1.4 (VCAP)
unnamed: C5.1, R9.2, U2.10 (Vin+)
unnamed: C5.2, R10.2, U2.9 (Vin-)
VBAT: C4.1, R7.2, R10.1; also elsewhere on the board

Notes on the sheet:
Overvoltage: 16.14V
~2.2mA
To be placed near power TP for GND Springs
Current Sensing
~16.4A Measurement Limit
6 * 0.005 = 30mV
6^2 * 0.005 = 0.18W
ADDR: 1000000
Reverse Polarity, Overvoltage Protection
Pin IN: closed / OFF Pin OUT: open / ON
Fc = 8.0 kHz
Pin Switch
Shunt
UVLO: Off = 9.69V, Restart = 10.54V
